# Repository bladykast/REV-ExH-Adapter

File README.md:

# ExH Type-C

This is the open-source repository for the [Expansion Hub Type-C Adapter Board](https://www.tindie.com/products/doubledip/expansion-hub-type-c-adapter/).

V3 is the most current branch (in development). The master branch is for V2 (currently sold). V1.1 is also available (nonfunctional but archived).

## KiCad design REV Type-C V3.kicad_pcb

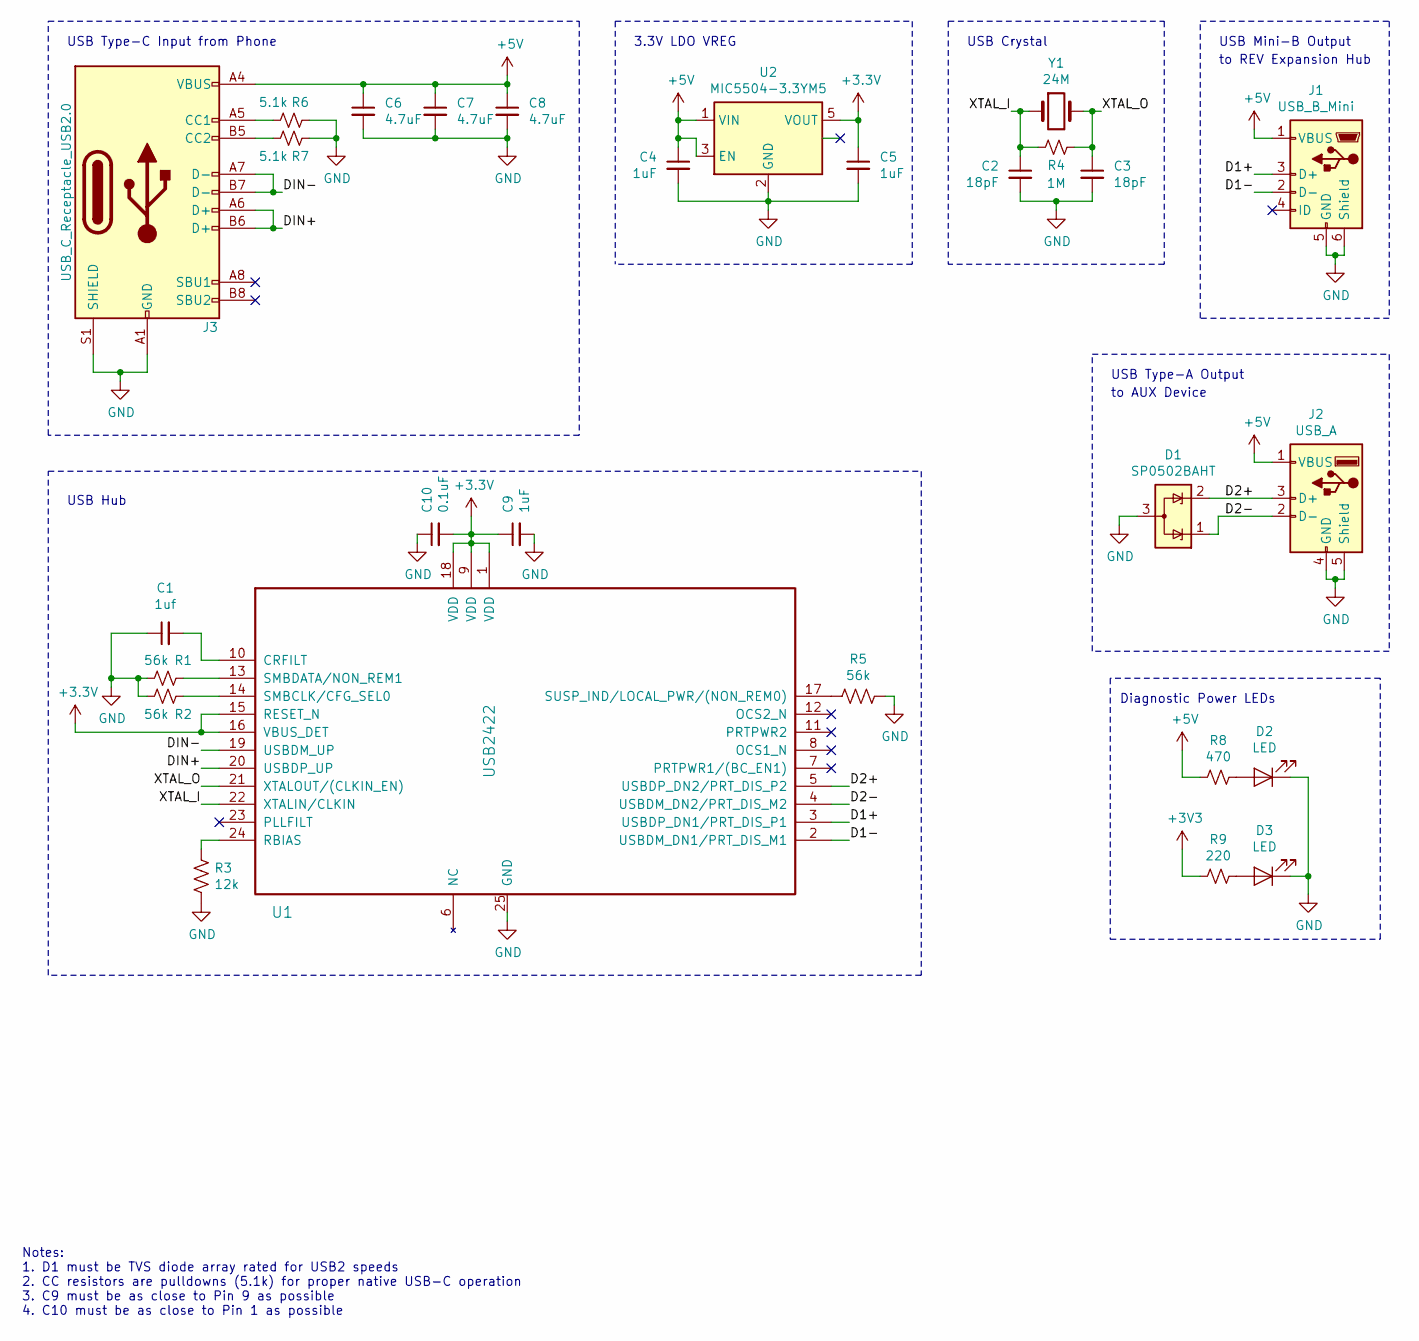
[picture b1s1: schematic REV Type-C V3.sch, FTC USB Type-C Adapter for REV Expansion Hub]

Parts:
C1: 1uf; C_0603_1608Metric
C2, C3: 18pF; C_0603_1608Metric
C4, C5, C9: 1uF; C_0603_1608Metric
C6, C7, C8: 4.7uF; C_0603_1608Metric
C10: 0.1uF; C_0603_1608Metric
D1: SP0502BAHT; SOT-23
D2, D3: LED; LED_0603_1608Metric
J1: USB_B_Mini; USB_Mini-B_Tensility_54-00023_Vertical
J2: USB_A; USB_A_Stewart_SS-52100-001_Horizontal
J3: USB_C_Receptacle_USB2.0; USB_C_Receptacle_GCT_USB4085
R1, R2, R5: 56k; R_0603_1608Metric
R3: 12k; R_0603_1608Metric
R4: 1M; R_0603_1608Metric
R6, R7: 5.1k; R_0603_1608Metric
R8: 470; R_0603_1608Metric
R9: 220; R_0603_1608Metric
U1: USB2422; QFN-24-1EP_4x4mm_P0.5mm_EP2.7x2.7mm_ThermalVias
U2: MIC5504-3.3YM5; SOT-23-5
Y1: 24M; Crystal_SMD_G8-2Pin_3.2x1.5mm_HandSoldering

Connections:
+5V: C4.1, C6.1, C7.1, C8.1, J1.1 (VBUS), J2.1 (VBUS), J3.A4 (VBUS), J3.A9 (VBUS), J3.B4 (VBUS), J3.B9 (VBUS), R8.2, U2.1 (VIN), U2.3 (EN)
/D1+: J1.3 (D+), U1.3 (USBDP_DN1/PRT_DIS_P1)
/D1-: J1.2 (D-), U1.2 (USBDM_DN1/PRT_DIS_M1)
/D2+: D1.2 (K), J2.3 (D+), U1.5 (USBDP_DN2/PRT_DIS_P2)
/D2-: D1.1 (K), J2.2 (D-), U1.4 (USBDM_DN2/PRT_DIS_M2)
/DIN+: J3.A6 (D+), J3.B6 (D+), U1.20 (USBDP_UP)
/DIN-: J3.A7 (D-), J3.B7 (D-), U1.19 (USBDM_UP)
/XTAL_I: C2.1, R4.2, U1.22 (XTALIN/CLKIN), Y1.1
/XTAL_O: C3.1, R4.1, U1.21 (XTALOUT/(CLKIN_EN)), Y1.2
GND: C1.1, C2.2, C3.2, C4.2, C5.2, C6.2, C7.2, C8.2, C9.2, C10.1, D1.3 (A), D2.1 (K), D3.1 (K), J1.5 (GND), J1.6 (Shield), J2.4 (GND), J2.5 (Shield), J3.A1 (GND), J3.A12 (GND), J3.B1 (GND), J3.B12 (GND), J3.S1 (SHIELD), R1.2, R2.2, R3.2, R5.1, R6.1, R7.1, U1.25 (GND), U2.2 (GND)
unnamed: C1.2, U1.10 (CRFILT)
unnamed: D2.2 (A), R8.1
unnamed: D3.2 (A), R9.1
unnamed: J3.A5 (CC1), R6.2
unnamed: J3.B5 (CC2), R7.2
unnamed: R1.1, U1.13 (SMBDATA/NON_REM1)
unnamed: R2.1, U1.14 (SMBCLK/CFG_SEL0)
unnamed: R3.1, U1.24 (RBIAS)
unnamed: R5.2, U1.17 (SUSP_IND/LOCAL_PWR/(NON_REM0))

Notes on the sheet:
Notes: 1. D1 must be TVS diode array rated for USB2 speeds 2. CC resistors are pulldowns (5.1k) for proper native USB-C operation 3. C9 must be as close to Pin 9 as possible 4. C10 must be as close to Pin 1 as possible
USB Type-C Input from Phone
3.3V LDO VREG
USB Crystal
USB Hub
USB Mini-B Output
to REV Expansion Hub
USB Type-A Output
to AUX Device
Diagnostic Power LEDs

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
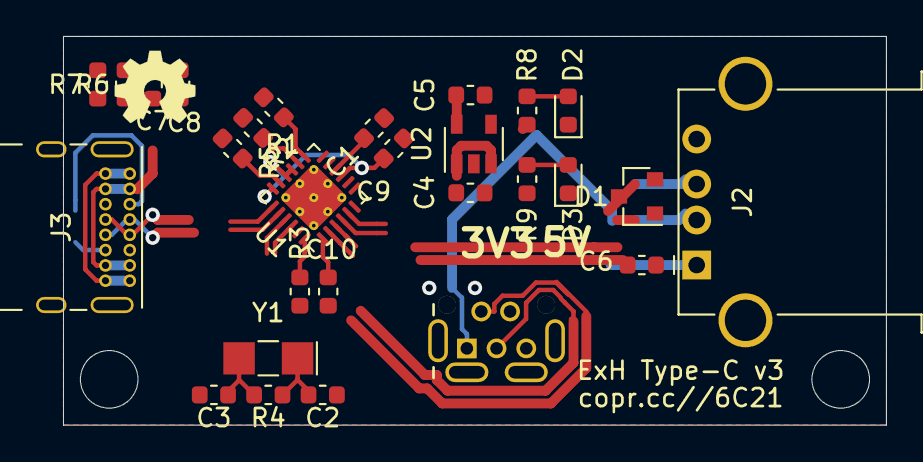
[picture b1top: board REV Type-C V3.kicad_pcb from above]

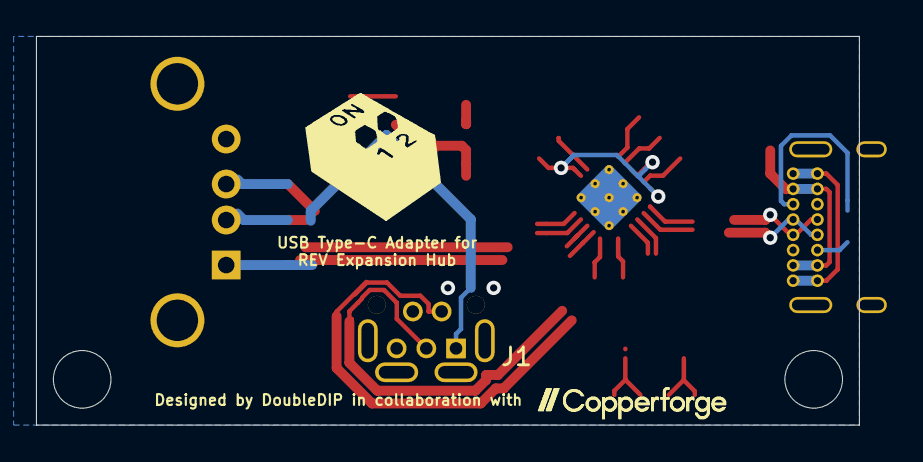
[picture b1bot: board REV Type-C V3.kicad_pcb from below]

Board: 2 copper layers, 45.7 x 21.6 mm, 30 parts (2 on the bottom side), 20 nets.

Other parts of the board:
DD: DD_IRL_NoLegs
LOGO: CU_Logo_LG

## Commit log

2019-07-06 Initial Files Commit
2019-08-19 Reorganize and prettify schematic
2019-08-19 Update "REV" styling in document comments
2019-08-24 Preliminary V3 files added
2019-08-24 Logo Files
2019-08-25 V3 Preliminary Files
2019-08-25 V1.1 Archive Upload
2019-08-25 Cleanup
2019-08-25 Branch Cleanup
2019-08-25 Fixed wrong Mini-B connector footprint
2019-08-25 USB2422 Symbol Files
2019-08-25 Fix USB hub symbol in schematic
2019-08-26 Add Copperforge P/N; potential one-sided V3 layout
